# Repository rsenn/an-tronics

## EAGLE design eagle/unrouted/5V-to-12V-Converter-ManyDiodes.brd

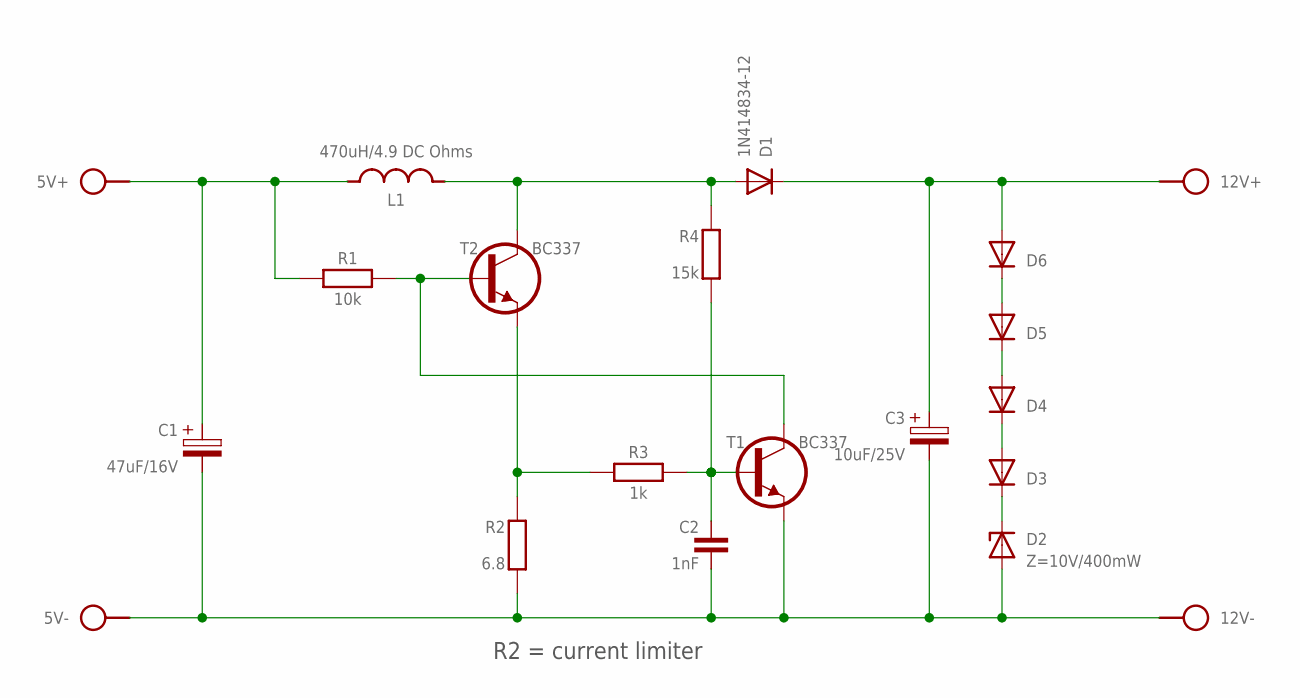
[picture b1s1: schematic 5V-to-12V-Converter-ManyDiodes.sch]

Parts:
5V: SPAD+--+; SPAD-+
12V: SPAD+-+-; SPAD+-
C1: 47uF/16V; E2.5-4/V
C2: 1nF; C050-020X036
C3: 10uF/25V; E2.5-4/V
D1: 1N414834-12; DO34-12
D2: Z=10V/400mW; DO35Z10/V
D3, D5: 1N4002-2.54A; DO35-2_54A
D4, D6: 1N4002-2.54; DO35-2_54
L1: 470uH/4.9 DC Ohms; ED16-X
R1: 10k; 0204/7-V
R2: 6.8; 0204/10
R3: 1k; 0204/10
R4: 15k; 0204/7-V
T1, T2: BC337; TO92-CBE

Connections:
unnamed: D2.C, D3.C
unnamed: 5V.2, C1.+, L1.1, R1.1
unnamed: 12V.2, C3.+, D1.C, D6.A
unnamed: 5V.1, 12V.1, C1.-, C2.2, C3.-, D2.A, R2.1 (2), T1.E
unnamed: R2.2 (1), R3.1, T2.E
unnamed: C2.1, R3.2, R4.1 (2), T1.B
unnamed: R1.2, T1.C, T2.B
unnamed: D1.A, L1.2, R4.2 (1), T2.C
unnamed: D3.A, D4.C
unnamed: D4.A, D5.C
unnamed: D5.A, D6.C

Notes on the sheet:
R2 = current limiter

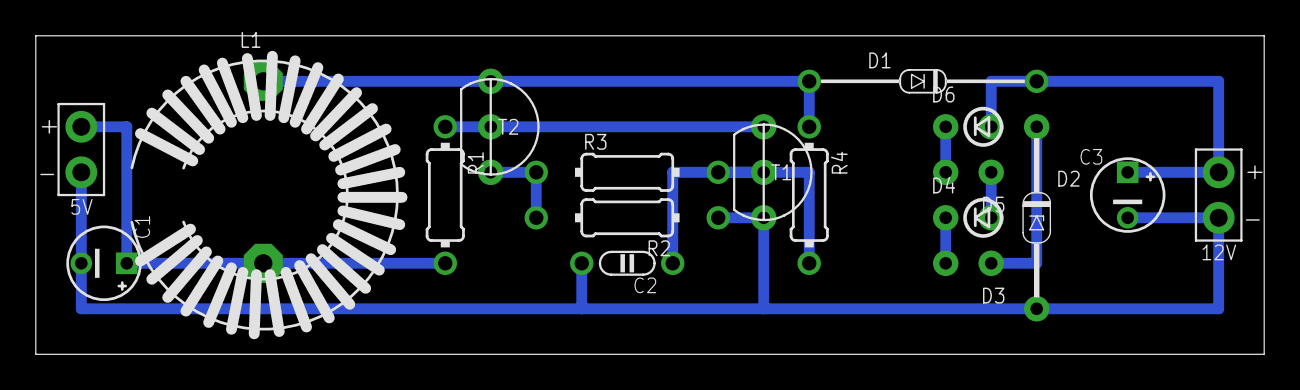
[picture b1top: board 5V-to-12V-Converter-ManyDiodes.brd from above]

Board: 2 copper layers, 68.6 x 17.8 mm, 18 parts (0 on the bottom side), 11 nets.

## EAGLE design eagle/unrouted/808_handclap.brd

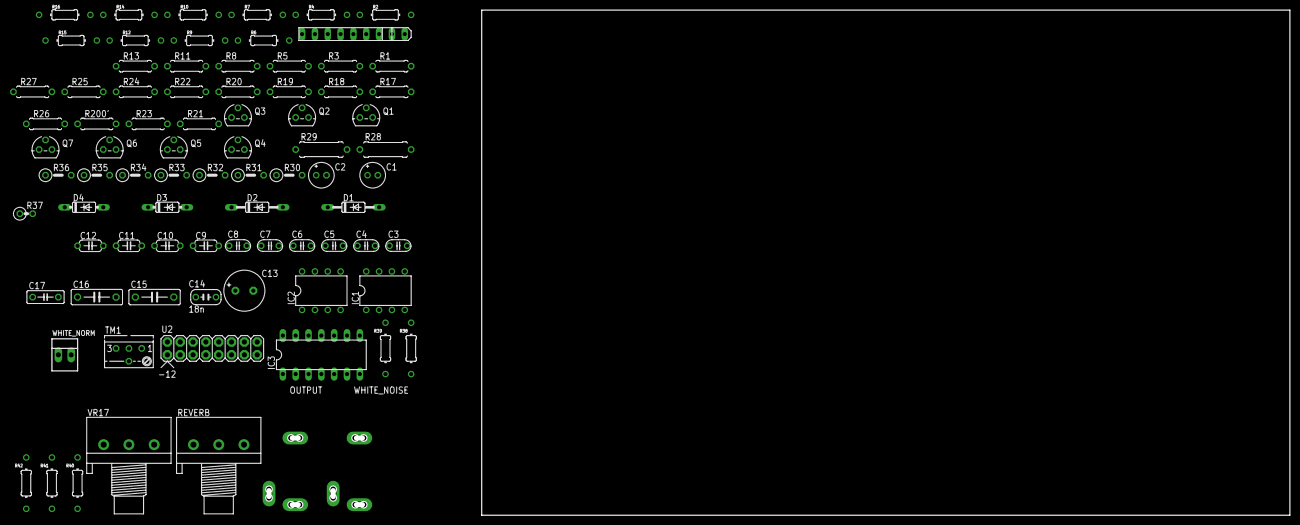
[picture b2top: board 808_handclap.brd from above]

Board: 2 copper layers, 202.1 x 100.0 mm, 82 parts (0 on the bottom side), 53 nets, no tracks yet.

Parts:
C1: .47/50; E2-5
C2: 1/50; E2-5
C3, C4, C8: 4.7n; C035-025X75
C5: 18n; C035-025X75
C6, C7: 1n; C035-025X75
C9: 22n; C050-024X044
C10: 47n; C050-024X044
C11: 27n; C050-024X044
C12: 220p; C050-024X044
C13: 33/6.3; E3,5-8
C14: 18n; C035-030X60
C15: 1.8n; C075-032X103
C16: 33n; C075-032X103
C17: 220p; C050-025X075
D1, D2: 1N4148DO35-10; DO35-10
D3, D4: 1N4148DO35-7; DO35-7
IC1, IC2: TL071P; DIL08
IC3: LM339N; DIL14
OUTPUT: AUDIO-JACK; ERTHENVAR-JACK-90DEG
Q1, Q2, Q3, Q7: 2N3904; TO92
Q4, Q5, Q6: 2N3906; TO92
R1: 470K; 0207/7
R2: 1M; 0204/10
R3: 39K; 0207/7
R4: 2K7; 0204/10
R5: 47K; 0207/7
R6: 1K; 0204/10
R7, R10: 68K; 0204/10
R8, R20, R23, R24, R200': 10K; 0207/7
R9: 27K; 0204/10
R11: 100K; 0207/7
R12: 10K; 0204/10
R13: 82K; 0207/7
R14: 330K; 0204/10
R15: 15K; 0204/10
R16: 470K; 0204/10
R17: 680; 0207/7
R18: 1M; 0207/7
R19: 4K7; 0207/7
R21: 22K; 0207/7
R22: 27K; 0207/7
R25: 15K; 0207/7
R26: 150K; 0207/7
R27: 330; 0207/7
R28: 4K7; 0309/10
R29: 47K; 0309/10
R30, R32: 4K7; 0207/5V
R31: 10K; 0207/5V
R33: 5K6; 0207/5V
R34: 82K; 0207/5V
R35, R36: 1K; 0207/5V
R37: 22K; 0207/2V
R38: 330R; 0204/10-V
R39: 15K; 0204/10-V
R40, R41: 1M; 0204/10-V
R42: 2K2; 0204/10-V
REVERB: 100k; 3RP/1610N
TM1: 10K(B); S64YW
U1: BA6110SIL; SIL09
U2: POWER; POWER_16
VR17: 100K(A); 3RP/1610N
WHITE_NOISE: AUDIO-JACK; ERTHENVAR-JACK-90DEG
WHITE_NORM: 22-23-2021

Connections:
+12V: IC1.7, IC2.7, Q7.1, R24.1, R25.1, U1.9, U2.9, U2.10
-12V: D4.A, IC1.4, IC2.4, IC3.12, Q3.3, Q6.1, R32.2, R37.2, R200'.2, TM1.A, U1.5, U2.1, U2.2
CP: R21.1, U2.15, U2.16
GND: C1.+, C2.-, C5.P$1, C10.2, C11.1, C14.P$2, IC1.3, IC3.3, OUTPUT.P$1, Q1.3, R5.1, R12.1, R13.1, R17.1, R18.1, R19.1, R20.1, R23.1, R33.2, R34.2, R35.1, R36.2, R38.2, R39.1, R42.2, TM1.E, U2.3, U2.4, U2.5, U2.6, U2.7, U2.8, WHITE_NOISE.P$1, WHITE_NORM.2
unnamed: OUTPUT.P$3, R6.1
unnamed: WHITE_NOISE.P$2, WHITE_NORM.1
unnamed: Q1.1, R31.1
unnamed: Q1.2, R21.2, R23.2
unnamed: C4.P$2, C9.1, IC1.6, R15.1, R26.2
unnamed: Q5.2, R30.1, R31.2
unnamed: C16.2, Q2.2, R2.1
unnamed: C5.P$2, D1.C, R40.2
unnamed: Q2.3, R38.1, R200'.1
unnamed: Q5.1, Q7.2, R22.1
unnamed: D1.A, D3.A, Q7.3
unnamed: C10.1, R2.2, R40.1
unnamed: C8.P$1, C14.P$1, Q2.1, R24.2
unnamed: C2.+, D3.C, R14.2
unnamed: Q6.2, R14.1, R29.2, R42.1
unnamed: R29.1, TM1.S
unnamed: C16.1, R15.2, R17.2
unnamed: D2.A, IC3.2, R34.1
unnamed: C3.P$2, C4.P$1, C15.2, R9.2, R12.2
unnamed: C3.P$1, IC1.2, R26.1
unnamed: C9.2, R3.2
unnamed: R3.1, R36.1, U1.2
unnamed: C8.P$2, REVERB.3
unnamed: R35.2, U1.1
unnamed: R8.1, U1.4
unnamed: R13.2, U1.6, U1.7
unnamed: C7.P$2, R11.1
unnamed: C7.P$1, U1.8
unnamed: IC3.5, IC3.6, R19.2, R28.1
unnamed: C1.-, D2.C, R27.1, R41.1
unnamed: Q4.2, R1.1, R39.2
unnamed: Q4.3, Q6.3, R25.2
unnamed: C6.P$1, IC3.1, IC3.4, R4.2
unnamed: Q4.1, R8.2
unnamed: Q3.1, R1.2, R27.2
unnamed: IC3.9, R28.2, R32.1
unnamed: C17.2, IC3.11, R41.2
unnamed: IC3.10, R4.1, R33.1
unnamed: IC3.8, R22.2, R37.1
unnamed: Q3.2, R7.1, R10.2
unnamed: C6.P$2, D4.C, R7.2
unnamed: C11.2, IC3.7, IC3.14, R18.2
unnamed: C17.1, IC3.13, R10.1, R20.2
unnamed: IC2.3, R5.2
unnamed: C12.2, IC2.2, R11.2, R16.2, REVERB.2, VR17.1
unnamed: C13.-, VR17.2
unnamed: C12.1, C13.+, IC2.6, R6.2, R16.1
TRIG: Q5.3, R30.2, U2.13, U2.14
WN: C15.1, R9.1, WHITE_NOISE.P$3

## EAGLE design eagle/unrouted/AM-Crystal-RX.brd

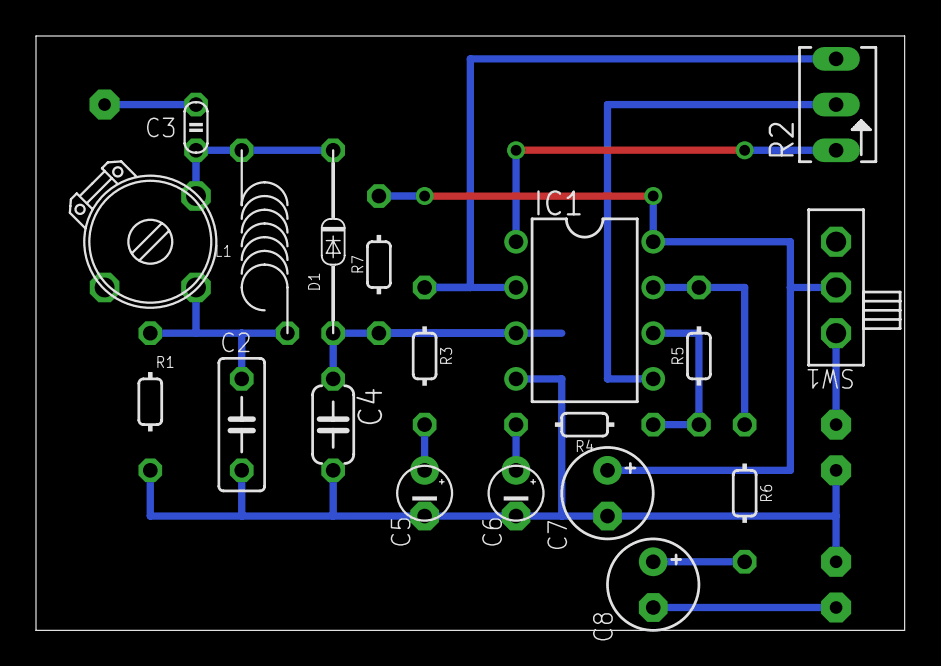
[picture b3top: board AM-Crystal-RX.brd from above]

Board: 2 copper layers, 48.3 x 33.0 mm, 24 parts (0 on the bottom side), 16 nets.

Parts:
ANT1: ANT; SPAD
BAT+: BAT+; SPAD
BAT-: BAT-; SPAD
C1: 5-18pF; TRIM-2222-808
C2: 10nF; C050-025X075
C3: C025-015X024
C4: 330pF; C050-024X044
C5, C6: 1uF; E2,5-3
C7, C8: 100uF; E2,5-5
D1: DETECTOR; DO34-10
IC1: LM358N; DIL08
L1: 0.1uH; L-04/10
R1: 10M; 0202/7-V
R2: 100k; B64Y
R3, R4: 0202/7
R5: 100k; 0202/7
R6: 100; 0202/7
R7: 10M; 0202/7
SP+: SPKR+; SPAD
SP-: SPKR-; SPAD
SW1: SL-SW-1P-2T-H; SLSW-1P2T-H

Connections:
GND: BAT-.1, C2.2, C4.2, C5.-, C6.-, C7.-, IC1.4, R1.1, SP-.1
unnamed: C4.1, D1.A, IC1.3, R7.2
unnamed: C7.+, IC1.8, R7.1, SW1.2
unnamed: C1.2, C2.1, L1.2, R1.2
unnamed: IC1.2, R2.A, R3.2
unnamed: C1.1, C3.2, D1.C, L1.1
unnamed: ANT1.1, C3.1
unnamed: IC1.1, R2.E
unnamed: IC1.5, R2.S
unnamed: IC1.7, R5.1, R6.2
unnamed: IC1.6, R4.2, R5.2
unnamed: C5.+, R3.1
unnamed: C6.+, R4.1
unnamed: C8.+, R6.1
unnamed: C8.-, SP+.1
unnamed: BAT+.1, SW1.1

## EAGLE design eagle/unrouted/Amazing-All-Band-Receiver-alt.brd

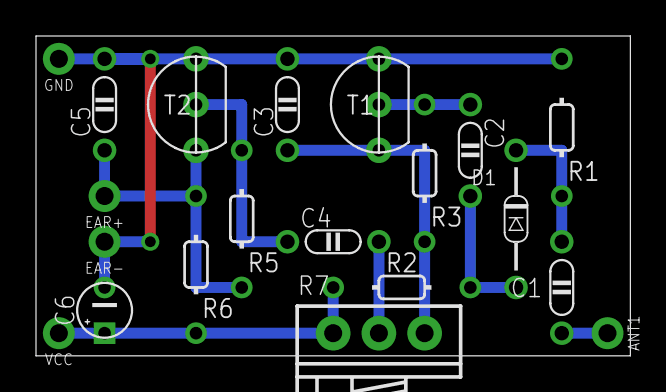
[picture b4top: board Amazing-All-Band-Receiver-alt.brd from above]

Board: 2 copper layers, 33.0 x 17.8 mm, 20 parts (0 on the bottom side), 10 nets.

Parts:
ANT1: ANT; SPAD
C1: 100p; C050-020X036/V
C2, C4: 10n; C050-020X036
C3, C5: 1n; C050-020X036
C6: 1u; E2,5-3
D1: OA79; DO34-7V
EAR+: SPAD
EAR-: SPAD
GND: SPAD
R1: 10k; 0202/7-V
R2: 10M; 0202/7
R3, R5: 10M; 0202/7-V
R6: 100k; 0202/7-V
R7: 100k; POT
T1, T2: BC547; TO92-CBE
VCC: SPAD

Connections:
AC: C1.2, D1.C, R1.2
ANT: ANT1.1, C1.1
DC: C2.2, D1.A, R2.1
GND: C3.2, C5.2, C6.-, EAR-.1, GND.1, R1.1, T1.E, T2.E
I1: C2.1, R3.1, T1.B
I2: C4.1, R5.1, T2.B
O1: C3.1, R3.2, R7.3, T1.C
O2: C5.1, EAR+.1, R5.2, R6.1, T2.C
VCC: C6.+, R2.2, R6.2, R7.1, VCC.1
VO1: C4.2, R7.2

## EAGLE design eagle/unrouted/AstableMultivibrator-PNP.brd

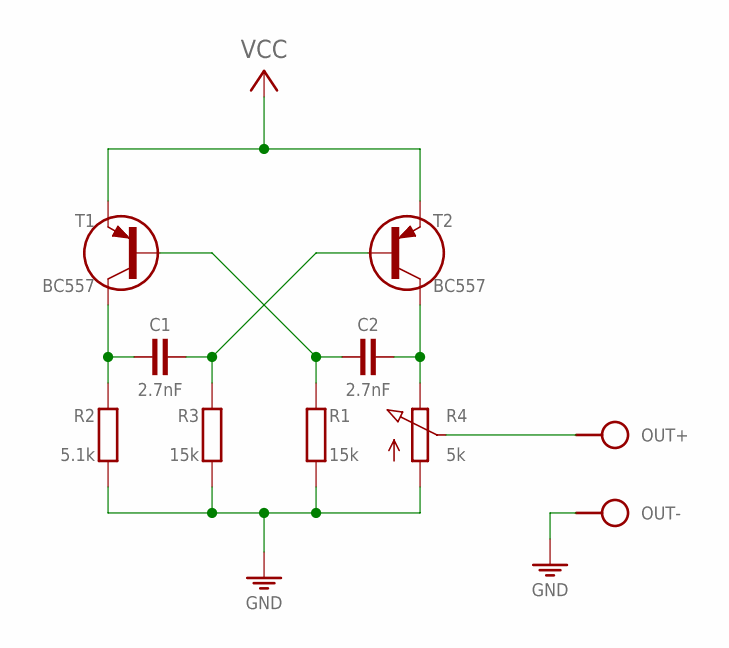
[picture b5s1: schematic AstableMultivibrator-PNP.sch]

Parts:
C1, C2: 2.7nF; C0750-020X044
J1: VCC_GNDPWR-L; PWR-L
OUT: SPAD+--+; SPAD-+
R1, R3: 15k; 0202/7-V
R2: 5.1k; 0202/7-V
R4: 5k; POT-V
T1, T2: BC557; TO92-CBE

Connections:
GND: J1.1 (GND), OUT.1, R1.1 (2), R2.1 (2), R3.1 (2), R4.A
unnamed: C2.2, R4.E, T2.C
unnamed: C1.1, R2.2 (1), T1.C
unnamed: C2.1, R1.2 (1), T1.B
unnamed: C1.2, R3.2 (1), T2.B
unnamed: OUT.2, R4.S
VCC: J1.2 (VCC), T1.E, T2.E

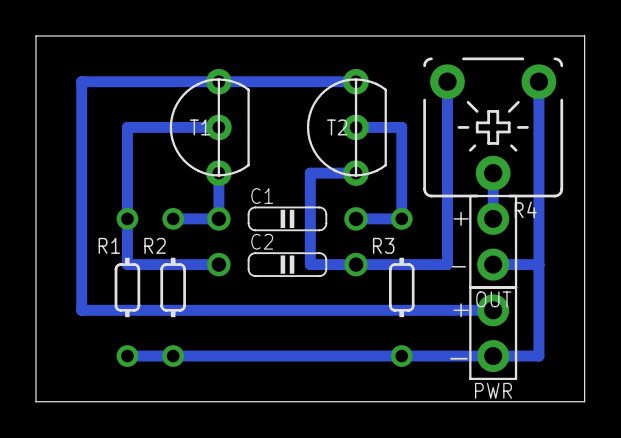
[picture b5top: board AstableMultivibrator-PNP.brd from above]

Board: 2 copper layers, 30.5 x 20.3 mm, 10 parts (0 on the bottom side), 7 nets.
